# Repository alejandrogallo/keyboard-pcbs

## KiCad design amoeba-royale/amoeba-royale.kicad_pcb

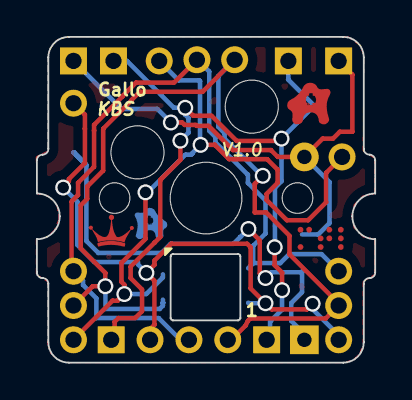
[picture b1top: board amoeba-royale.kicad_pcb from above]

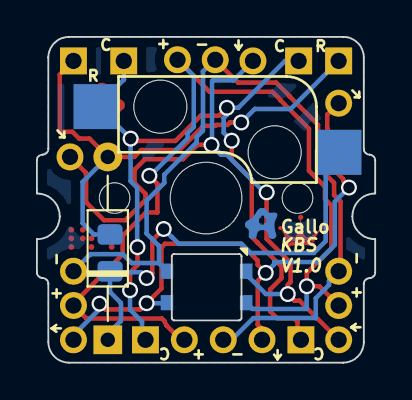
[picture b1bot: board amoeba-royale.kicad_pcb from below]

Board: 2 copper layers, 18.8 x 18.1 mm, 28 parts (5 on the bottom side), 7 nets.

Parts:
Amoeba-Logo: G***; amoeba-logo
Amoeba-Logo-Small: G***; amoeba-logo-small
D0: DIODE; D_DO-35_SOD27_P10.16mm_Horizontal
D1: DIODE; D_0805_2012Metric_Pad1.15x1.40mm_HandSolder
DIN0:0, DIN0:1: Conn_01x01_Female; SolderWirePad_1x01_Drill0.9mm_round
DIN0:3: Conn_01x01_Male; SolderWirePad_1x01_Drill0.9mm_round
DOUT0:0, DOUT0:2: Conn_01x01_Male; SolderWirePad_1x01_Drill0.9mm_round
DOUT0:1: Conn_01x01_Female; SolderWirePad_1x01_Drill0.9mm_round
LED0: SK6812MINI; LED_SK6812MINI_PLCC4_3.5x3.5mm_P1.75mm_hole
Royale: G***; royale
S0: MX1A; Kailh_MX_Socket
SC0:0, SC0:1, SC1:0, SC1:1: Conn_01x01; SolderWirePad_1x01_Drill0.9mm_square
SR0, SR1: Conn_01x01; SolderWirePad_1x01_Drill0.9mm_square
VDD0:0, VDD0:3: Conn_01x01_Male; SolderWirePad_1x01_Drill0.9mm_round
VDD0:1, VDD0:2: Conn_01x01_Female; SolderWirePad_1x01_Drill0.9mm_round
VSS0:0, VSS0:3: Conn_01x01_Male; SolderWirePad_1x01_Drill0.9mm_round
VSS0:1, VSS0:2: Conn_01x01_Female; SolderWirePad_1x01_Drill0.9mm_round
mtl-braille: G***; mtl-braille

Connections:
/DIN: DIN0:0.1, DIN0:1.1, DIN0:3.1, LED0.3
/DOUT: DOUT0:0.1, DOUT0:1.1, DOUT0:2.1, LED0.1
/VDD: LED0.4, VDD0:0.1, VDD0:1.1, VDD0:2.1, VDD0:3.1
/VSS: LED0.2, VSS0:0.1, VSS0:1.1, VSS0:2.1, VSS0:3.1
/key/SC0: S0.2, SC0:0.1, SC0:1.1, SC1:0.1, SC1:1.1
/key/SR0: D0.2, D1.2, SR0.1, SR1.1
/key/switch/N-SD0: D0.1, D1.1, S0.1

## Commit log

2020-08-29 Remove tear pads for jlcpcb
